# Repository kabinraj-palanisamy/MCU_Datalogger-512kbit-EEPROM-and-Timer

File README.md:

# MCU_Datalogger 512k EEPROM and Timer

## MCU Datalogger mit Data und Memory
A professional-grade, low-power embedded datalogging system designed for high-capacity non-volatile storage and precision timestamping

## Project Overview
This project features a robust hardware architecture built around the ATmega328P-AU microcontroller. It is specifically engineered for industrial logging applications requiring reliable data retention and modular sensor integration via I2C, UART, and ICSP interfaces.

## Key Hardware Features

* **Core Processor:** High-performance, low-power ATmega328P-AU 8-bit MCU running at 16 MHz.
* **Precision Timing:** Integrated DS1337S Real-Time Clock (RTC) paired with a dedicated 32.768 kHz crystal for accurate time-series data collection.
* **High-Capacity Storage:** Dual 24LC1025 I2C EEPROM modules providing expanded non-volatile memory for long-term logging

### Modular Connectivity
* **UART:** For serial debugging and telemetry.
* **I2C Bus:** Centralized communication for RTC and memory modules.
* **ICSP:** Standard 6-pin header for in-circuit programming and debugging.

### Hardware Robustness 
* **Power Stability:** Strategically placed decoupling capacitors.
* **Diagnostics:** Integrated power status LEDs for immediate hardware feedback.
* **Enclosure:** Standardized mounting hole placement for secure industrial integration.
  
## System Architecture
The design prioritizes signal integrity and power management.
* **EDA Tool:** KiCad 10.0.0.
* **Voltage Domains:** Optimized power flags to ensure consistent Vcc distribution.
* **Communication:** Synchronous I2C bus with dedicated 4.7k/10k pull-up resistors for reliable multi-slave communication.

### Version 1.1.0

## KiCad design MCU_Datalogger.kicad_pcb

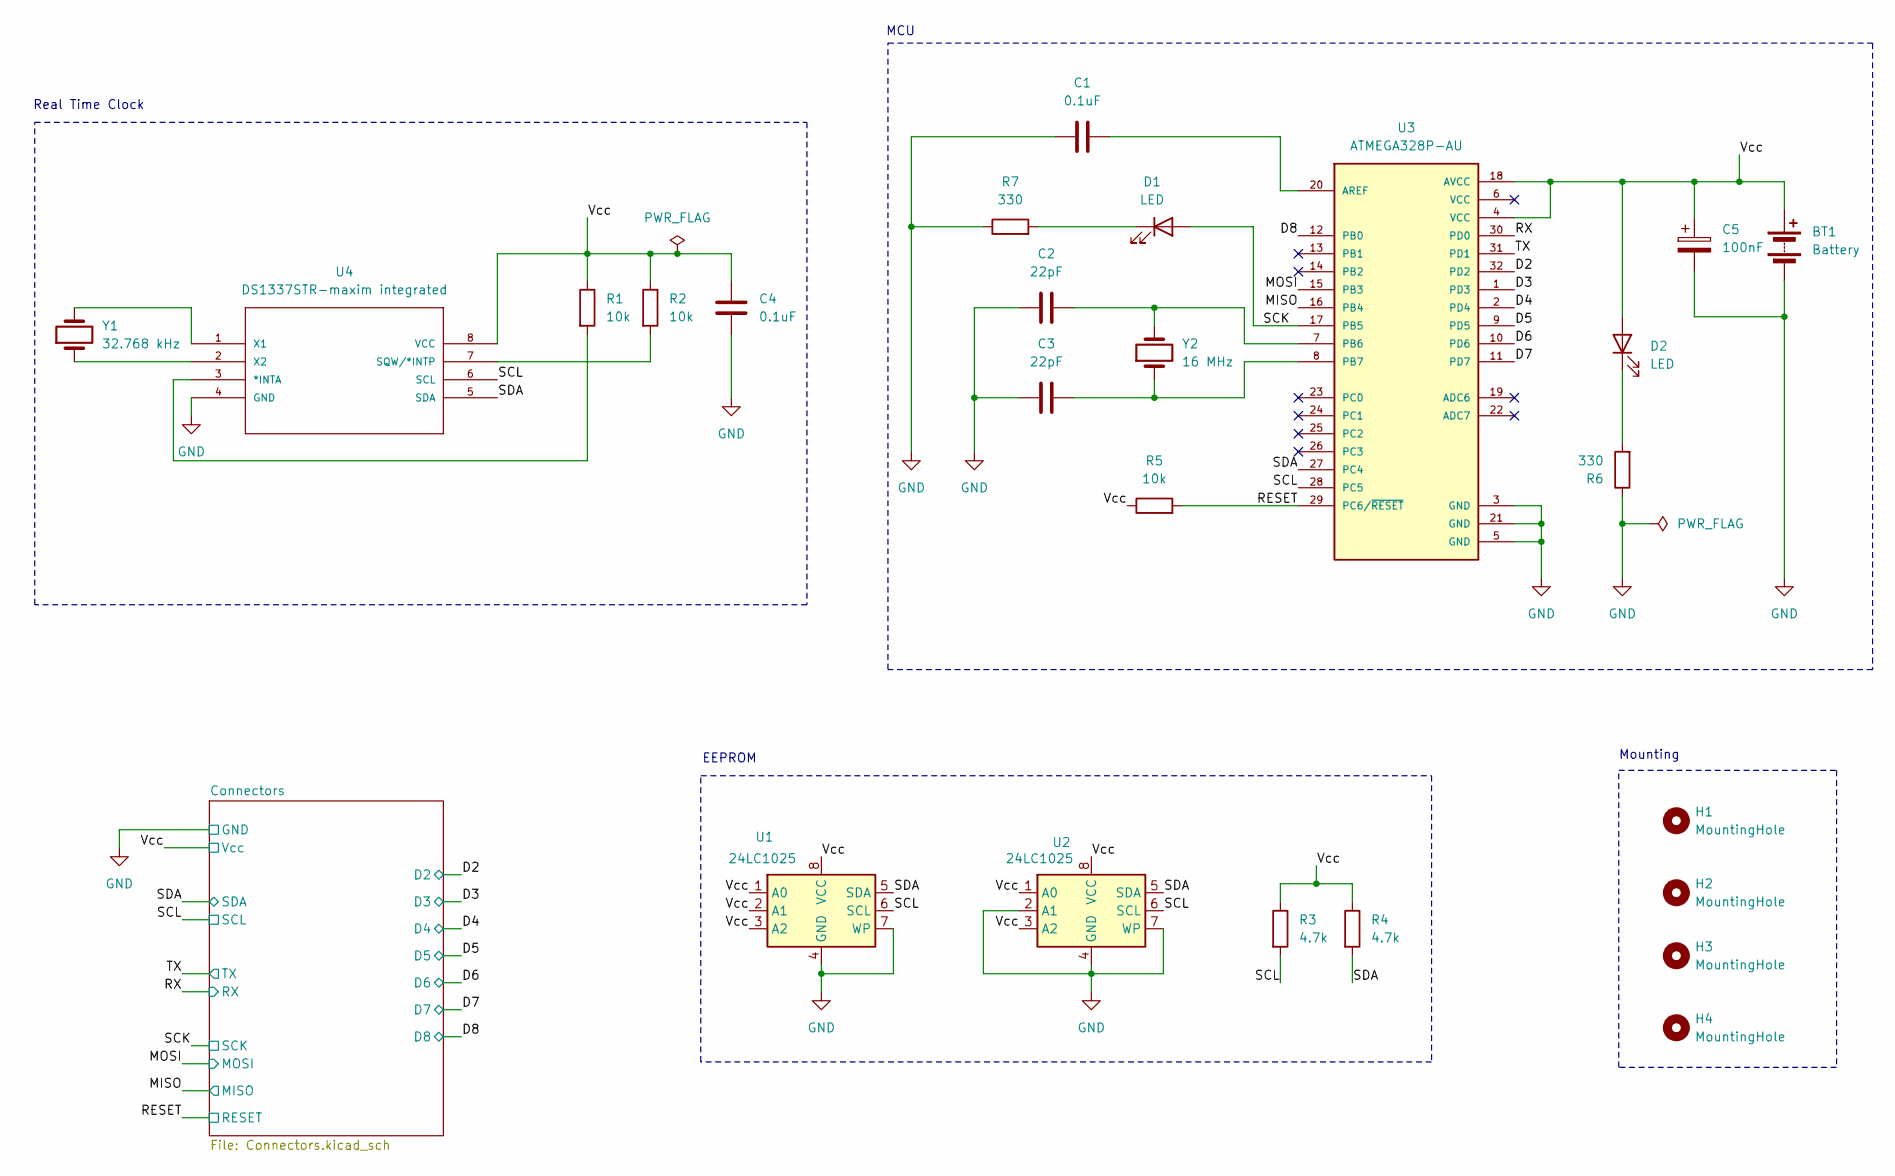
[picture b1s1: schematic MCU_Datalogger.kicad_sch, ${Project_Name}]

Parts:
BT1: Battery; PinHeader_1x02_P2.54mm_Vertical
C1, C4: 0.1uF; C_0805_2012Metric
C2, C3: 22pF; C_0805_2012Metric
C5: 100nF; C_0805_2012Metric
D1, D2: LED; LED_0805_2012Metric
H1, H2, H3, H4: MountingHole; MountingHole_2.1mm
R1, R2, R5: 10k; R_0805_2012Metric
R3, R4: 4.7k; R_0805_2012Metric
R6, R7: 330; R_0805_2012Metric
U1, U2: 24LC1025; SOIC-8_5.3x5.3mm_P1.27mm
U3: ATMEGA328P-AU; MCU_ATmega328P-AU; PARTREV 8271A
U4: DS1337STR-maxim integrated; DS1337S-Maxim Intergrated; MANUFACTURER_PART_NUMBER DS1337S+T&R
Y1: 32.768 kHz; Crystal_SMD_Abracon_ABM3-2Pin_5.0x3.2mm_HandSoldering
Y2: 16 MHz; Crystal_SMD_Abracon_ABM3-2Pin_5.0x3.2mm_HandSoldering

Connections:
/D2: U3.32 (PD2); also elsewhere on the board
/D3: U3.1 (PD3); also elsewhere on the board
/D4: U3.2 (PD4); also elsewhere on the board
/D5: U3.9 (PD5); also elsewhere on the board
/D6: U3.10 (PD6); also elsewhere on the board
/D7: U3.11 (PD7); also elsewhere on the board
/D8: U3.12 (PB0); also elsewhere on the board
/MISO: U3.16 (PB4); also elsewhere on the board
/MOSI: U3.15 (PB3); also elsewhere on the board
/RESET: R5.2, U3.29 (PC6/~RESET); also elsewhere on the board
/RX: U3.30 (PD0); also elsewhere on the board
/SCK: D1.2 (A), U3.17 (PB5); also elsewhere on the board
/SCL: R3.2, U1.6 (SCL), U2.6 (SCL), U3.28 (PC5), U4.6 (SCL); also elsewhere on the board
/SDA: R4.2, U1.5 (SDA), U2.5 (SDA), U3.27 (PC4), U4.5 (SDA); also elsewhere on the board
/TX: U3.31 (PD1); also elsewhere on the board
/Vcc: BT1.1 (+), C4.1, C5.1, D2.2 (A), R1.1, R2.1, R3.1, R4.1, R5.1, U1.1 (A0), U1.2 (A1), U1.3 (A2), U1.8 (VCC), U2.1 (A0), U2.3 (A2), U2.8 (VCC), U3.4 (VCC), U3.18 (AVCC), U4.8 (VCC); also elsewhere on the board
GND: BT1.2 (-), C1.1, C2.1, C3.1, C4.2, C5.2, R6.1, R7.1, U1.4 (GND), U1.7 (WP), U2.2 (A1), U2.4 (GND), U2.7 (WP), U3.3 (GND), U3.5 (GND), U3.21 (GND), U4.4 (GND); also elsewhere on the board
unnamed: D1.1 (K), R7.2
unnamed: D2.1 (K), R6.2
unnamed: C1.2, U3.20 (AREF)
unnamed: C2.2, U3.7 (PB6), Y2.2
unnamed: C3.2, U3.8 (PB7), Y2.1
unnamed: R1.2, U4.3 (*INTA)
unnamed: R2.2, U4.7 (SQW/*INTP)
unnamed: U4.1 (X1), Y1.2
unnamed: U4.2 (X2), Y1.1

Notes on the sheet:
Real Time Clock
EEPROM
MCU
Mounting

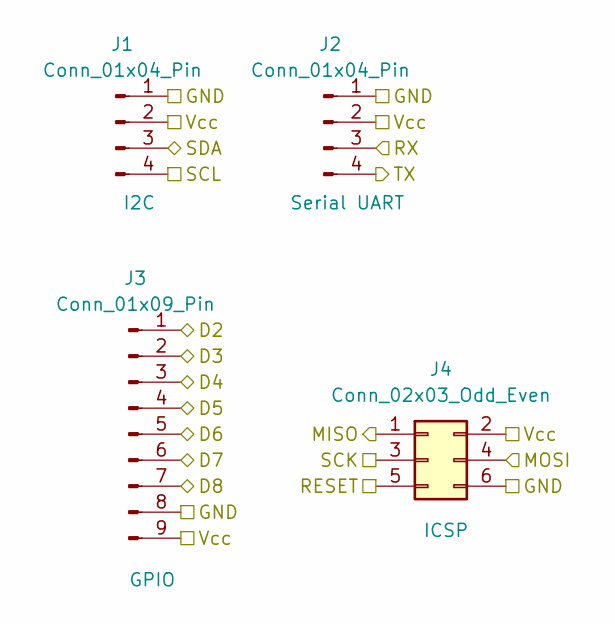
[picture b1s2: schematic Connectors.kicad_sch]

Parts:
J1, J2: Conn_01x04_Pin; PinHeader_1x04_P2.54mm_Vertical
J3: Conn_01x09_Pin; PinHeader_1x09_P2.54mm_Vertical
J4: Conn_02x03_Odd_Even; PinHeader_2x03_P2.54mm_Vertical

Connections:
/D2: J3.1; also elsewhere on the board
/D3: J3.2; also elsewhere on the board
/D4: J3.3; also elsewhere on the board
/D5: J3.4; also elsewhere on the board
/D6: J3.5; also elsewhere on the board
/D7: J3.6; also elsewhere on the board
/D8: J3.7; also elsewhere on the board
/MISO: J4.1; also elsewhere on the board
/MOSI: J4.4; also elsewhere on the board
/RESET: J4.5; also elsewhere on the board
/RX: J2.3; also elsewhere on the board
/SCK: J4.3; also elsewhere on the board
/SCL: J1.4; also elsewhere on the board
/SDA: J1.3; also elsewhere on the board
/TX: J2.4; also elsewhere on the board
/Vcc: J1.2, J2.2, J3.9, J4.2; also elsewhere on the board
GND: J1.1, J2.1, J3.8, J4.6; also elsewhere on the board

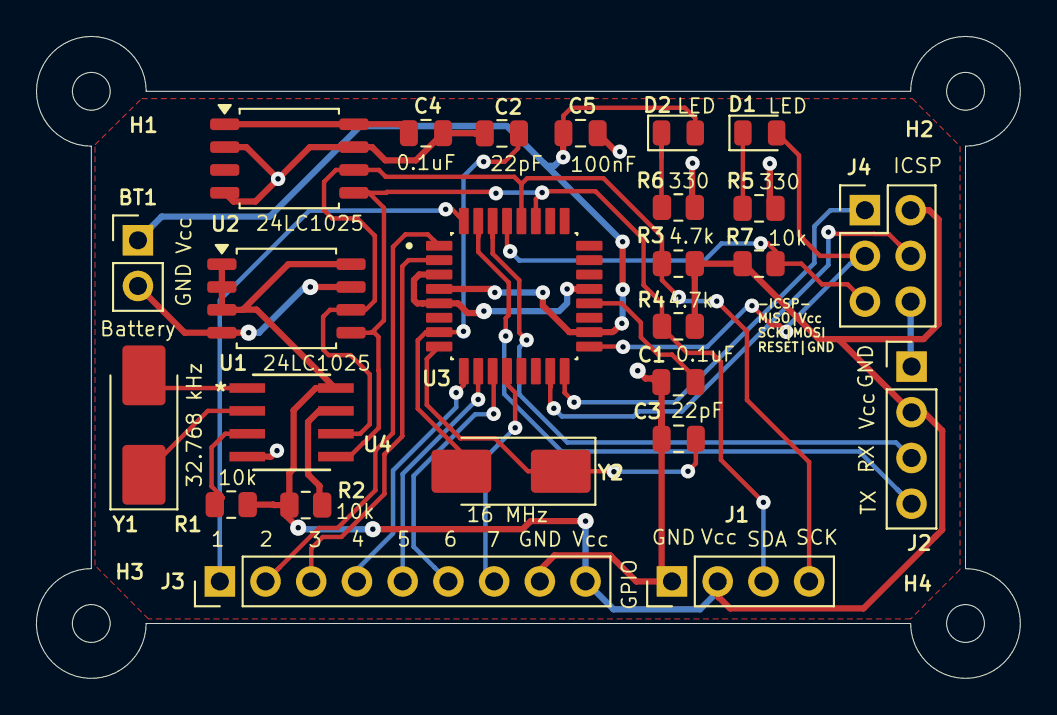
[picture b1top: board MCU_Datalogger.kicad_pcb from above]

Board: 2 copper layers, 54.7 x 35.7 mm, 29 parts (0 on the bottom side), 26 nets.

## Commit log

2026-03-26 Add files via upload
    2 Layer PCB
2026-03-29 3D Images, Schematic PDF, STEP & Gerbers
